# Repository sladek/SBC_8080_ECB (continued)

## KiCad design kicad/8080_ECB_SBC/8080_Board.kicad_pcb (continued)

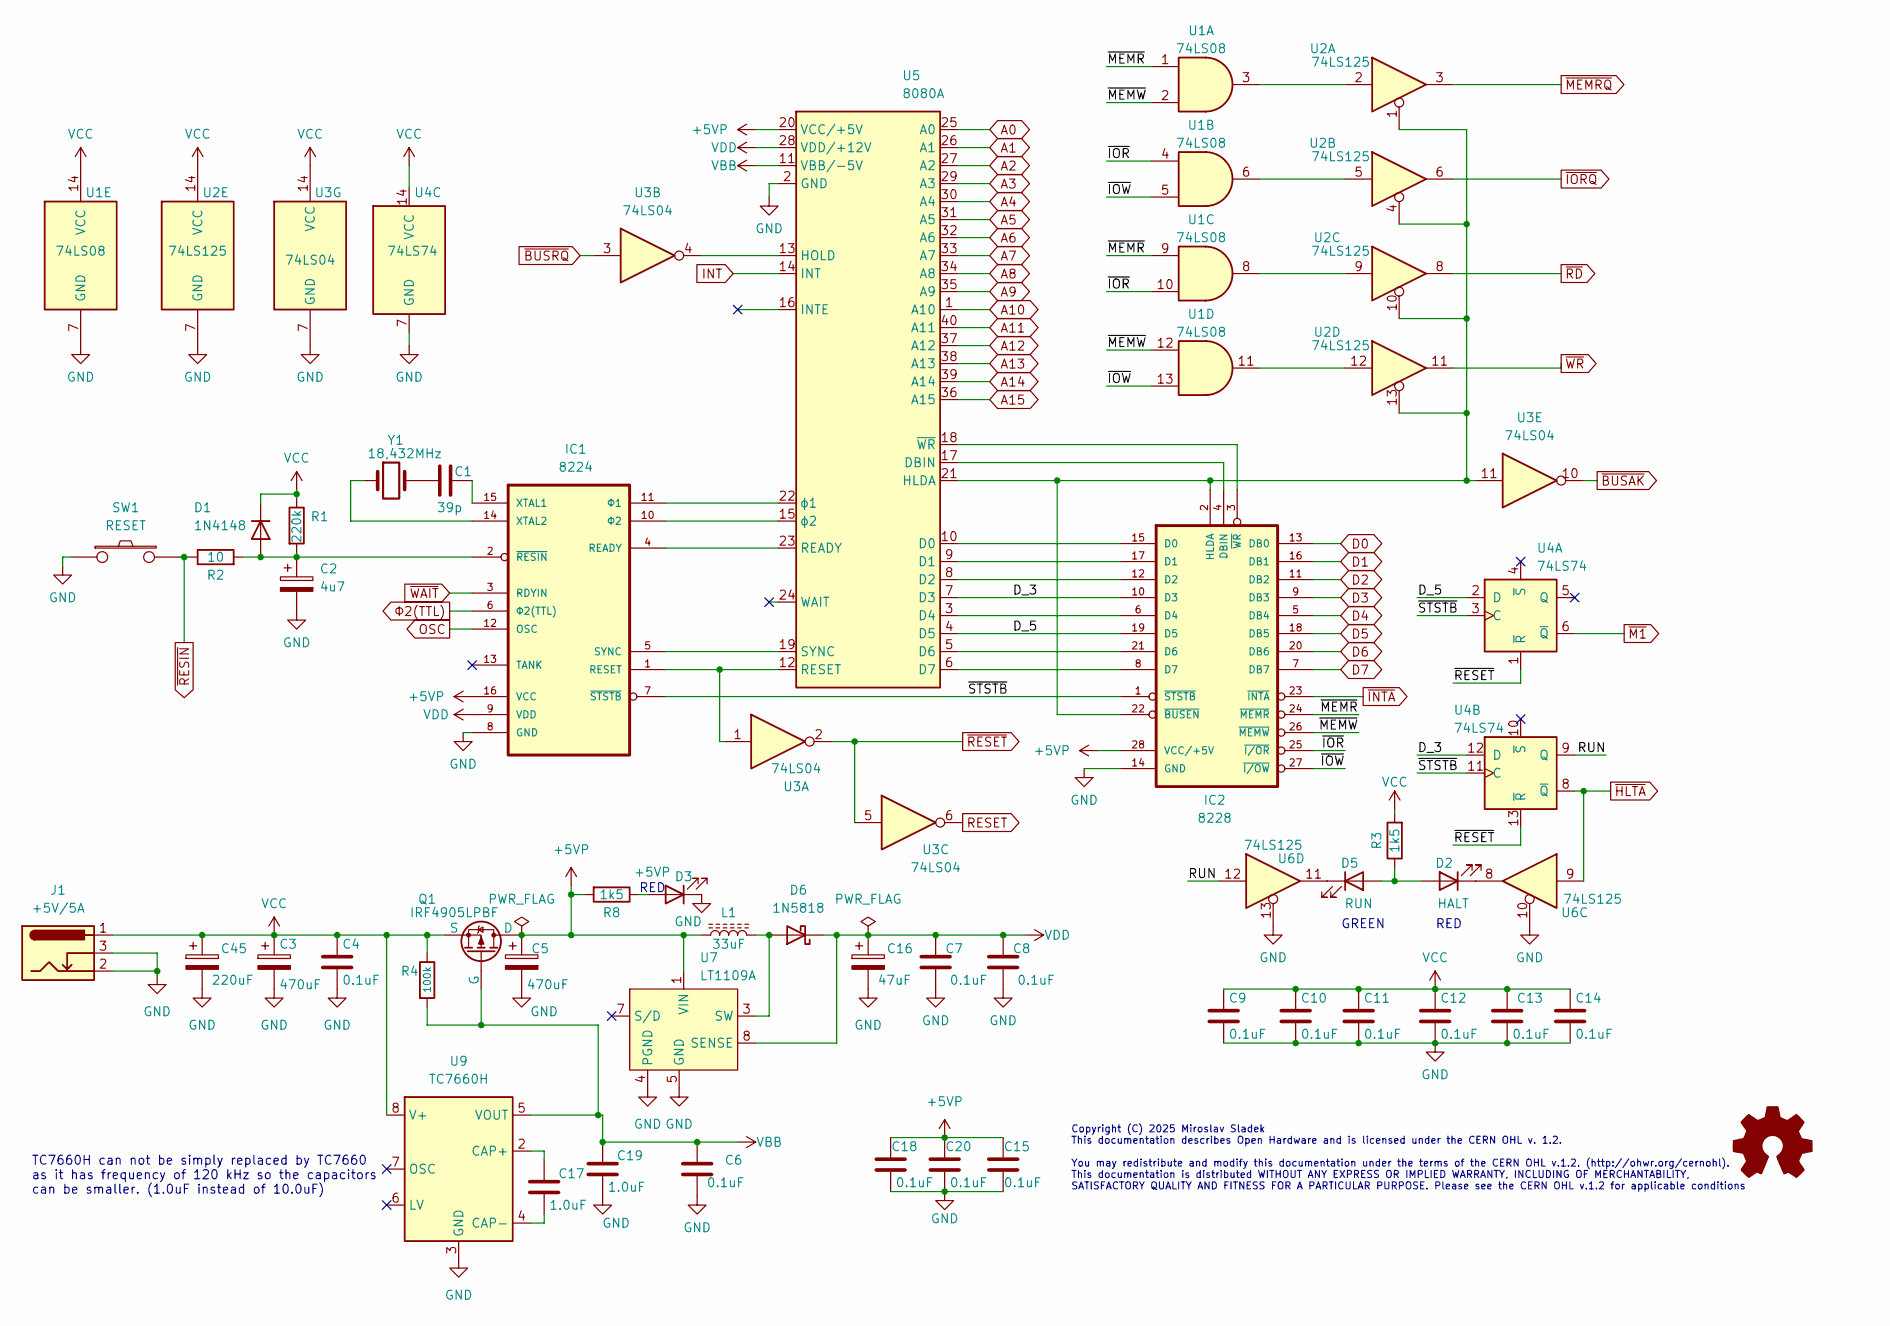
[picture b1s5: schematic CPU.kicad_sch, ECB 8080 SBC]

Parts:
C1: 39p; C_Disc_D5.0mm_W2.5mm_P2.50mm
C2: 4u7; CP_Radial_D4.0mm_P1.50mm
C3, C5: 470uF; CP_Radial_D6.3mm_P2.50mm
C4, C6, C7, C8, C9, C10, C11, C12, C13, C14, C15, C18, C20: 0.1uF; C_Disc_D4.3mm_W1.9mm_P5.00mm
C16: 47uF; CP_Radial_D5.0mm_P2.00mm
C17, C19: 1.0uF; C_Disc_D4.7mm_W2.5mm_P5.00mm
C45: 220uF; CP_Radial_D5.0mm_P2.00mm
D1: 1N4148; D_DO-35_SOD27_P7.62mm_Horizontal
D2: HALT; LED_D3.0mm
D3: +5VP; LED_D3.0mm
D5: RUN; LED_D3.0mm
D6: 1N5818; D_DO-41_SOD81_P10.16mm_Horizontal
IC1: 8224; DIP-16_W7.62mm_Socket
IC2: 8228; DIP-28_W15.24mm_Socket
J1: +5V/5A; 694106301002_1
L1: 33uF; L_Radial_D6.0mm_P4.00mm
Q1: IRF4905LPBF; TO254P483X1016X1501-3P
R1: 220k; R_Axial_DIN0204_L3.6mm_D1.6mm_P7.62mm_Horizontal
R2: 10; R_Axial_DIN0204_L3.6mm_D1.6mm_P7.62mm_Horizontal
R3, R8: 1k5; R_Axial_DIN0204_L3.6mm_D1.6mm_P7.62mm_Horizontal
R4: 100k; R_Axial_DIN0204_L3.6mm_D1.6mm_P7.62mm_Horizontal
SW1: RESET; PinHeader_1x02_P2.54mm_Vertical
U1: 74LS08; DIP-14_W7.62mm_Socket
U2, U6: 74LS125; DIP-14_W7.62mm_Socket
U3: 74LS04; DIP-14_W7.62mm_Socket
U4: 74LS74; DIP-14_W7.62mm_Socket
U5: 8080A; DIP-40_W15.24mm_Socket
U7: LT1109A; DIP-8_W7.62mm_Socket
U9: TC7660H; DIP-8_W7.62mm_Socket
Y1: 18,432MHz; Crystal_HC49-U_Vertical

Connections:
+5VP: C5.1, C15.1, C18.1, C20.1, IC1.16 (VCC), IC2.28 (VCC/+5V), L1.1, Q1.3 (D), R8.2, U5.20 (VCC/+5V), U7.1 (VIN)
/CPU/D_3: IC2.10 (D3), U4.12 (D), U5.7 (D3)
/CPU/D_5: IC2.19 (D5), U4.2 (D), U5.4 (D5)
/CPU/RUN: U4.9 (Q), U6.12
/CPU/~IOR: IC2.25 (~I/OR), U1.4, U1.10
/CPU/~IOW: IC2.27 (~I/OW), U1.5, U1.13
/CPU/~MEMR: IC2.24 (~MEMR), U1.1, U1.9
/CPU/~MEMW: IC2.26 (~MEMW), U1.2, U1.12
/CPU/~STSTB: IC1.7 (~STSTB), IC2.1 (~STSTB), U4.3 (C), U4.11 (C)
A0: U5.25 (A0); also elsewhere on the board
A1: U5.26 (A1); also elsewhere on the board
A2: U5.27 (A2); also elsewhere on the board
A3: U5.29 (A3); also elsewhere on the board
A4: U5.30 (A4); also elsewhere on the board
A5: U5.31 (A5); also elsewhere on the board
A6: U5.32 (A6); also elsewhere on the board
A7: U5.33 (A7); also elsewhere on the board
A8: U5.34 (A8); also elsewhere on the board
A9: U5.35 (A9); also elsewhere on the board
A10: U5.1 (A10); also elsewhere on the board
A11: U5.40 (A11); also elsewhere on the board
A12: U5.37 (A12); also elsewhere on the board
A13: U5.38 (A13); also elsewhere on the board
A14: U5.39 (A14); also elsewhere on the board
A15: U5.36 (A15); also elsewhere on the board
D0: IC2.13 (DB0); also elsewhere on the board
D1: IC2.16 (DB1); also elsewhere on the board
D2: IC2.11 (DB2); also elsewhere on the board
D3: IC2.9 (DB3); also elsewhere on the board
D4: IC2.5 (DB4); also elsewhere on the board
D5: IC2.18 (DB5); also elsewhere on the board
D6: IC2.20 (DB6); also elsewhere on the board
D7: IC2.7 (DB7); also elsewhere on the board
INT: U5.14 (INT); also elsewhere on the board
unnamed: C1.1, Y1.2
unnamed: C2.1, D1.2 (A), IC1.2 (~RESIN), R1.2, R2.2
unnamed: D2.2 (A), D5.2 (A), R3.1
unnamed: D2.1 (K), U6.8
unnamed: D3.2 (A), R8.1
unnamed: D5.1 (K), U6.11
unnamed: D6.2 (A), L1.2, U7.3 (SW)
unnamed: IC1.4 (READY), U5.23 (READY)
unnamed: IC1.1 (RESET), U3.1, U5.12 (RESET)
unnamed: IC1.5 (SYNC), U5.19 (SYNC)
unnamed: C1.2, IC1.15 (XTAL1)
unnamed: IC1.14 (XTAL2), Y1.1
unnamed: IC1.11 (Φ1), U5.22 (ϕ1)
unnamed: IC1.10 (Φ2), U5.15 (ϕ2)
unnamed: IC2.15 (D0), U5.10 (D0)
unnamed: IC2.17 (D1), U5.9 (D1)
unnamed: IC2.12 (D2), U5.8 (D2)
unnamed: IC2.6 (D4), U5.3 (D4)
unnamed: IC2.21 (D6), U5.5 (D6)
unnamed: IC2.8 (D7), U5.6 (D7)
unnamed: IC2.4 (DBIN), U5.17 (DBIN)
unnamed: IC2.2 (HLDA), IC2.22 (~BUSEN), U2.1, U2.4, U2.10, U2.13, U3.11, U5.21 (HLDA)
unnamed: IC2.3 (~WR), U5.18 (~WR)
unnamed: U1.3, U2.2
unnamed: U1.6, U2.5
unnamed: U1.8, U2.9
unnamed: U1.11, U2.12
unnamed: U3.4, U5.13 (HOLD)
unnamed: C17.1, U9.2 (CAP+)
unnamed: C17.2, U9.4 (CAP-)
OSC: IC1.12 (OSC); also elsewhere on the board
RESET: U3.6; also elsewhere on the board
VBB: C6.1, C19.1, Q1.1 (G), R4.2, U5.11 (VBB/-5V), U9.5 (VOUT)
VCC: C3.1, C4.1, C9.1, C10.1, C11.1, C12.1, C13.1, C14.1, C45.1, D1.1 (K), J1.1, Q1.2 (S), R1.1, R3.2, R4.1, U1.14 (VCC), U2.14 (VCC), U3.14 (VCC), U4.14 (VCC), U9.8 (V+); also elsewhere on the board
VDD: C7.1, C8.1, C16.1, D6.1 (K), IC1.9 (VDD), U5.28 (VDD/+12V), U7.8 (SENSE)
~BUSAK: U3.10; also elsewhere on the board
~BUSRQ: U3.3; also elsewhere on the board
~HLTA: U4.8 (~Q), U6.9; also elsewhere on the board
~INTA: IC2.23 (~INTA); also elsewhere on the board
~IORQ: U2.6; also elsewhere on the board
~M1: U4.6 (~Q); also elsewhere on the board
~MEMRQ: U2.3; also elsewhere on the board
~RD: U2.8; also elsewhere on the board
~RESET: U3.2, U3.5, U4.1 (~R), U4.13 (~R); also elsewhere on the board
~RESIN: R2.1, SW1.2; also elsewhere on the board
~WAIT: IC1.3 (RDYIN); also elsewhere on the board
~WR: U2.11; also elsewhere on the board
Φ2(TTL): IC1.6 (Φ2(TTL)); also elsewhere on the board

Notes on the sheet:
GREEN
RED
TC7660H can not be simply replaced by TC7660 as it has frequency of 120 kHz so the capacitors can be smaller. (1.0uF instead of 10.0uF)
Copyright (C) 2025 Miroslav Sladek This documentation describes Open Hardware and is licensed under the CERN OHL v. 1.2. You may redistribute and modify this documentation under the terms of the CERN OHL v.1.2. (http://ohwr.org/cernohl). This documentation is distributed WITHOUT ANY EXPRESS OR IMPL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

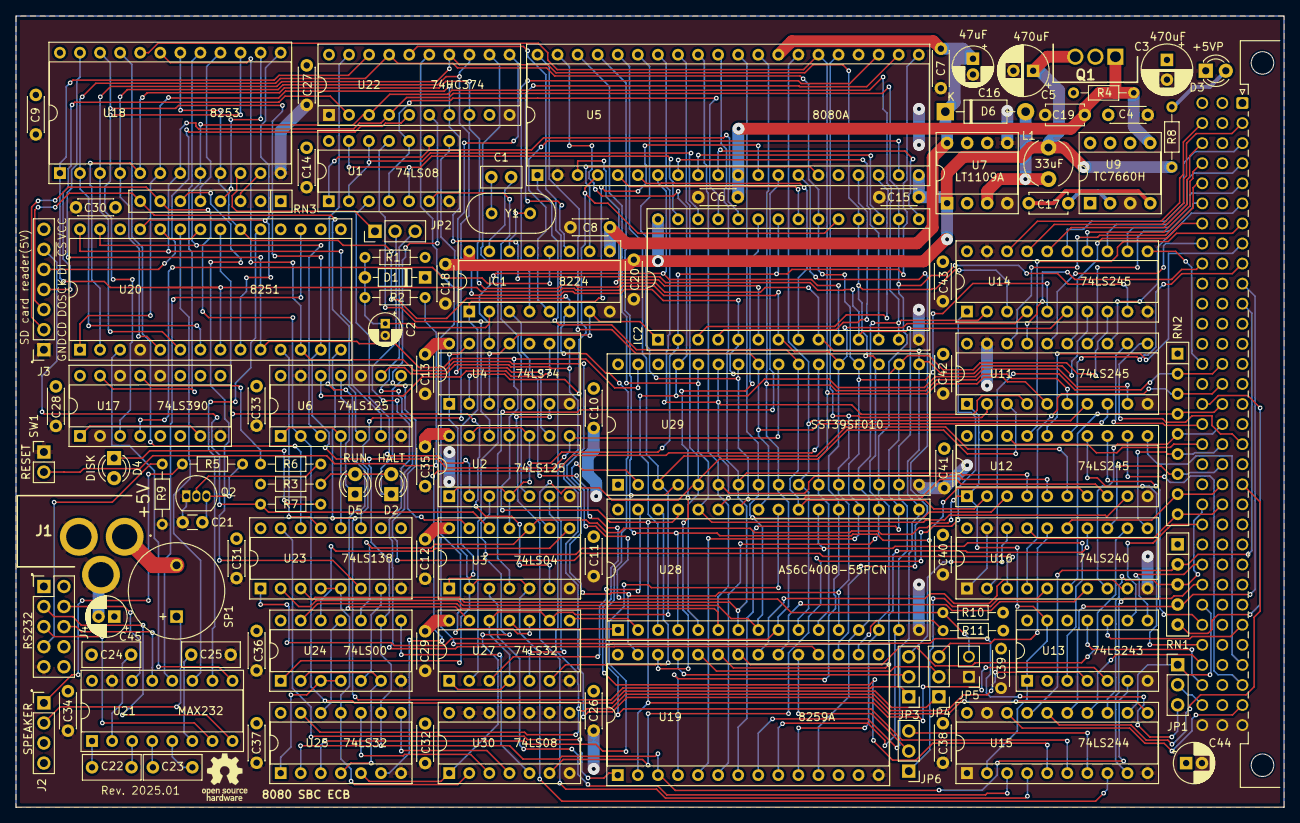
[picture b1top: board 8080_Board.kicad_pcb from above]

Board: 2 copper layers, 160.5 x 100.2 mm, 111 parts (0 on the bottom side), 207 nets.

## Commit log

2025-04-20 Fixed REDMA.md
2025-04-20 Added pdf schematics.
2025-04-21 Added introduction and PDF links to README.md
2025-04-21 Added power supply information to README.md
2025-05-31 cleanup
